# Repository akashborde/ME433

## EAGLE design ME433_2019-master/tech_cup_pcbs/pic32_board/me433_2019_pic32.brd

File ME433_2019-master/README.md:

# ME433_2019

Go to the wiki to see the syllabus and schedule.

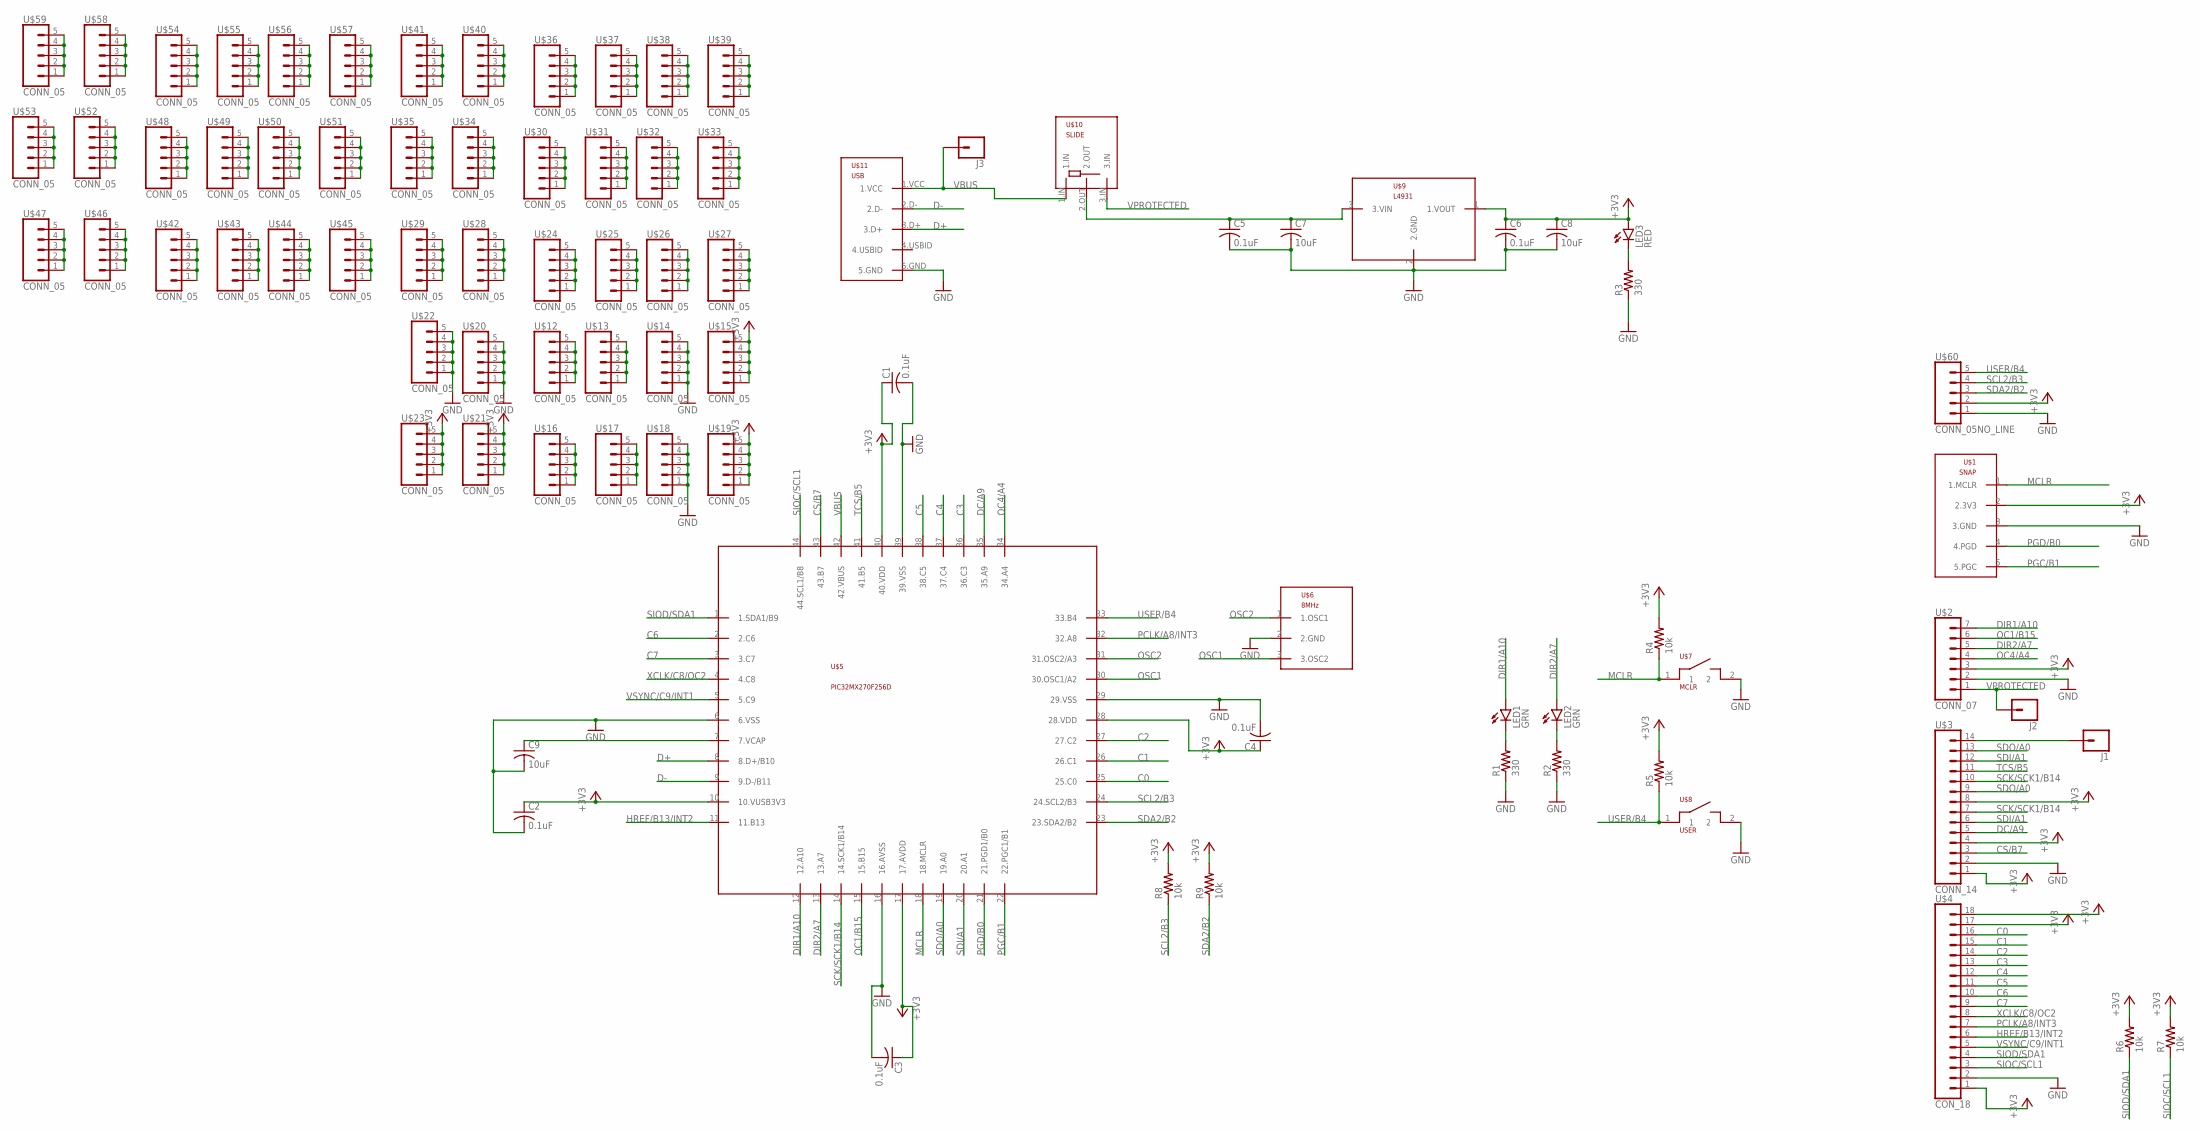
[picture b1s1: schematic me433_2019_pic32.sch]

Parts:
C1, C2, C3, C4, C5, C6: 0.1uF; C025-030X050
C7, C8, C9: 10uF; C025-030X050
J1, J2, J3: CONN_01; 1X01
LED1, LED2: GRN; LED3MM
LED3: RED; LED3MM
R1, R2, R3: 330; 0207/10
R4, R5, R6, R7, R8, R9: 10k; 0207/10
U$1: SNAP
U$2: CONN_07; 1X07
U$3: CONN_14; 1X14
U$4: CON_18; 1X18
U$5: PIC32MX270F256D; TQFP44
U$6: 8MHz; OSC
U$7: MCLR; PB
U$8: USER; PB
U$9: L4931
U$10: SLIDE
U$11: USB
U$12, U$13, U$14, U$15, U$16, U$17, U$18, U$19, U$20, U$21, U$22, U$23, U$24, U$25, U$26, U$27, U$28, U$29, U$30, U$31, U$32, U$33, U$34, U$35, U$36, U$37, U$38, U$39, U$40, U$41, U$42, U$43, U$44, U$45, U$46, U$47, U$48, U$49, U$50, U$51, U$52, U$53, U$54, U$55, U$56, U$57, U$58, U$59: CONN_05; 1X05
U$60: CONN_05NO_LINE; 1X05_NO_LINE

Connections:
+3V3: C1.1, C2.1, C3.1, C4.1, C6.1, C8.1, LED3.A, R4.2, R5.2, R6.2, R7.2, R8.2, R9.2, U$1.2 (2.3V3), U$2.3, U$3.1, U$3.4, U$3.8, U$4.1, U$4.17, U$4.18, U$5.10 (10.VUSB3V3), U$5.17 (17.AVDD), U$5.28 (28.VDD), U$5.40 (40.VDD), U$9.1 (1.VOUT), U$15.1, U$15.2, U$15.3, U$15.4, U$15.5, U$19.1, U$19.2, U$19.3, U$19.4, U$19.5, U$21.1, U$21.2, U$21.3, U$21.4, U$21.5, U$23.1, U$23.2, U$23.3, U$23.4, U$23.5, U$60.2
C0: U$4.16, U$5.25 (25.C0)
C1: U$4.15, U$5.26 (26.C1)
C2: U$4.14, U$5.27 (27.C2)
C3: U$4.13, U$5.36 (36.C3)
C4: U$4.12, U$5.37 (37.C4)
C5: U$4.11, U$5.38 (38.C5)
C6: U$4.10, U$5.2 (2.C6)
C7: U$4.9, U$5.3 (3.C7)
CS/B7: U$3.3, U$5.43 (43.B7)
D+: U$5.8 (8.D+/B10), U$11.3.D+
D-: U$5.9 (9.D-/B11), U$11.2.D-
DC/A9: U$3.5, U$5.35 (35.A9)
DIR1/A10: LED1.A, U$2.7, U$5.12 (12.A10)
DIR2/A7: LED2.A, U$2.5, U$5.13 (13.A7)
GND: C1.2, C2.2, C3.2, C4.2, C5.2, C6.2, C7.2, C8.2, C9.2, R1.1, R2.1, R3.1, U$1.3 (3.GND), U$2.2, U$3.2, U$4.2, U$5.6 (6.VSS), U$5.16 (16.AVSS), U$5.29 (29.VSS), U$5.39 (39.VSS), U$6.2 (2.GND), U$7.2, U$8.2, U$9.2 (2.GND), U$11.5.GND, U$14.1, U$14.2, U$14.3, U$14.4, U$14.5, U$18.1, U$18.2, U$18.3, U$18.4, U$18.5, U$20.1, U$20.2, U$20.3, U$20.4, U$20.5, U$22.1, U$22.2, U$22.3, U$22.4, U$22.5, U$60.1
HREF/B13/INT2: U$4.6, U$5.11 (11.B13)
MCLR: R4.1, U$1.1 (1.MCLR), U$5.18 (18.MCLR), U$7.1
unnamed: C9.1, U$5.7 (7.VCAP)
unnamed: LED1.K (C), R1.2
unnamed: LED2.K (C), R2.2
unnamed: J1.1, U$3.14
unnamed: C5.1, C7.1, U$9.3 (3.VIN), U$10.2.OUT
unnamed: U$12.1, U$12.2, U$12.3, U$12.4, U$12.5
unnamed: U$13.1, U$13.2, U$13.3, U$13.4, U$13.5
unnamed: LED3.K (C), R3.2
unnamed: U$16.1, U$16.2, U$16.3, U$16.4, U$16.5
unnamed: U$17.1, U$17.2, U$17.3, U$17.4, U$17.5
unnamed: U$24.1, U$24.2, U$24.3, U$24.4, U$24.5
unnamed: U$25.1, U$25.2, U$25.3, U$25.4, U$25.5
unnamed: U$26.1, U$26.2, U$26.3, U$26.4, U$26.5
unnamed: U$27.1, U$27.2, U$27.3, U$27.4, U$27.5
unnamed: U$28.1, U$28.2, U$28.3, U$28.4, U$28.5
unnamed: U$29.1, U$29.2, U$29.3, U$29.4, U$29.5
unnamed: U$30.1, U$30.2, U$30.3, U$30.4, U$30.5
unnamed: U$31.1, U$31.2, U$31.3, U$31.4, U$31.5
unnamed: U$32.1, U$32.2, U$32.3, U$32.4, U$32.5
unnamed: U$33.1, U$33.2, U$33.3, U$33.4, U$33.5
unnamed: U$34.1, U$34.2, U$34.3, U$34.4, U$34.5
unnamed: U$35.1, U$35.2, U$35.3, U$35.4, U$35.5
unnamed: U$36.1, U$36.2, U$36.3, U$36.4, U$36.5
unnamed: U$37.1, U$37.2, U$37.3, U$37.4, U$37.5
unnamed: U$38.1, U$38.2, U$38.3, U$38.4, U$38.5
unnamed: U$39.1, U$39.2, U$39.3, U$39.4, U$39.5
unnamed: U$40.1, U$40.2, U$40.3, U$40.4, U$40.5
unnamed: U$41.1, U$41.2, U$41.3, U$41.4, U$41.5
unnamed: U$42.1, U$42.2, U$42.3, U$42.4, U$42.5
unnamed: U$43.1, U$43.2, U$43.3, U$43.4, U$43.5
unnamed: U$44.1, U$44.2, U$44.3, U$44.4, U$44.5
unnamed: U$45.1, U$45.2, U$45.3, U$45.4, U$45.5
unnamed: U$46.1, U$46.2, U$46.3, U$46.4, U$46.5
unnamed: U$47.1, U$47.2, U$47.3, U$47.4, U$47.5
unnamed: U$48.1, U$48.2, U$48.3, U$48.4, U$48.5
unnamed: U$49.1, U$49.2, U$49.3, U$49.4, U$49.5
unnamed: U$50.1, U$50.2, U$50.3, U$50.4, U$50.5
unnamed: U$51.1, U$51.2, U$51.3, U$51.4, U$51.5
unnamed: U$52.1, U$52.2, U$52.3, U$52.4, U$52.5
unnamed: U$53.1, U$53.2, U$53.3, U$53.4, U$53.5
unnamed: U$54.1, U$54.2, U$54.3, U$54.4, U$54.5
unnamed: U$55.1, U$55.2, U$55.3, U$55.4, U$55.5
unnamed: U$56.1, U$56.2, U$56.3, U$56.4, U$56.5
unnamed: U$57.1, U$57.2, U$57.3, U$57.4, U$57.5
unnamed: U$58.1, U$58.2, U$58.3, U$58.4, U$58.5
unnamed: U$59.1, U$59.2, U$59.3, U$59.4, U$59.5
OC1/B15: U$2.6, U$5.15 (15.B15)
OC4/A4: U$2.4, U$5.34 (34.A4)
OSC1: U$5.30 (30.OSC1/A2), U$6.3 (3.OSC2)
OSC2: U$5.31 (31.OSC2/A3), U$6.1 (1.OSC1)
PCLK/A8/INT3: U$4.7, U$5.32 (32.A8)
PGC/B1: U$1.5 (5.PGC), U$5.22 (22.PGC1/B1)
PGD/B0: U$1.4 (4.PGD), U$5.21 (21.PGD1/B0)
SCK/SCK1/B14: U$3.7, U$3.10, U$5.14 (14.SCK1/B14)
SCL2/B3: R8.1, U$5.24 (24.SCL2/B3), U$60.4
SDA2/B2: R9.1, U$5.23 (23.SDA2/B2), U$60.3
SDI/A1: U$3.6, U$3.12, U$5.20 (20.A1)
SDO/A0: U$3.9, U$3.13, U$5.19 (19.A0)
SIOC/SCL1: R7.1, U$4.3, U$5.44 (44.SCL1/B8)
SIOD/SDA1: R6.1, U$4.4, U$5.1 (1.SDA1/B9)
TCS/B5: U$3.11, U$5.41 (41.B5)
USER/B4: R5.1, U$5.33 (33.B4), U$8.1, U$60.5
VBUS: J3.1, U$5.42 (42.VBUS), U$10.1.IN, U$11.1.VCC
VPROTECTED: J2.1, U$2.1, U$10.3.IN
VSYNC/C9/INT1: U$4.5, U$5.5 (5.C9)
XCLK/C8/OC2: U$4.8, U$5.4 (4.C8)

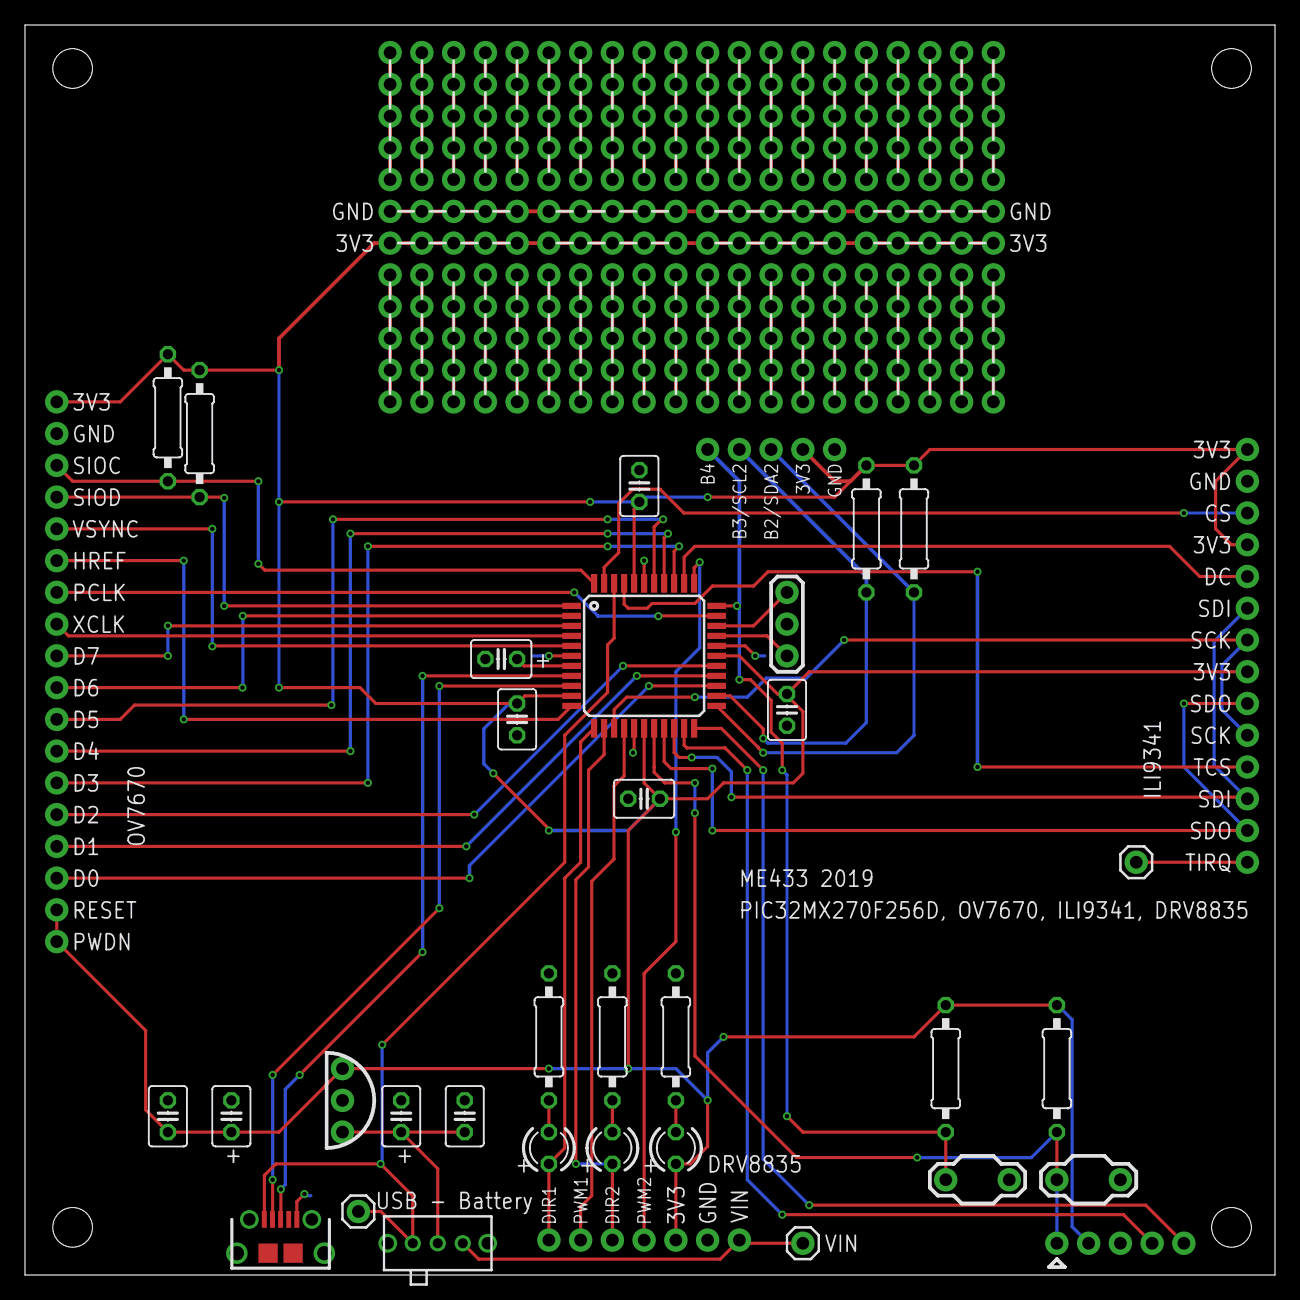
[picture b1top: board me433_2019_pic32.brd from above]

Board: 2 copper layers, 100.0 x 100.0 mm, 84 parts (0 on the bottom side), 84 nets.

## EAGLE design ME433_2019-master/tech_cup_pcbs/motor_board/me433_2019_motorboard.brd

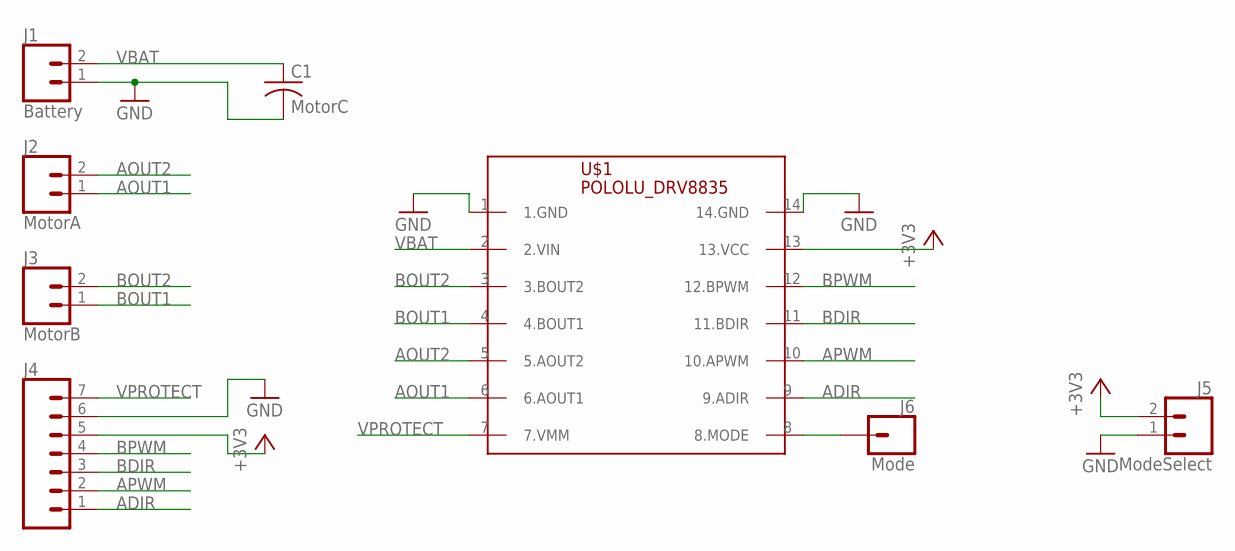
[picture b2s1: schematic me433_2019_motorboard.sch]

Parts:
C1: MotorC; C050-030X075
J1: Battery; 1X02
J2: MotorA; 1X02
J3: MotorB; 1X02
J4: CONN_07; 1X07
J5: ModeSelect; 1X02
J6: Mode; 1X01
U$1: POLOLU_DRV8835; DIL14

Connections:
+3V3: J4.5, J5.2, U$1.13 (13.VCC)
ADIR: J4.1, U$1.9 (9.ADIR)
AOUT1: J2.1, U$1.6 (6.AOUT1)
AOUT2: J2.2, U$1.5 (5.AOUT2)
APWM: J4.2, U$1.10 (10.APWM)
BDIR: J4.3, U$1.11 (11.BDIR)
BOUT1: J3.1, U$1.4 (4.BOUT1)
BOUT2: J3.2, U$1.3 (3.BOUT2)
BPWM: J4.4, U$1.12 (12.BPWM)
GND: C1.2, J1.1, J4.6, J5.1, U$1.1 (1.GND), U$1.14 (14.GND)
unnamed: J6.1, U$1.8 (8.MODE)
VBAT: C1.1, J1.2, U$1.2 (2.VIN)
VPROTECT: J4.7, U$1.7 (7.VMM)

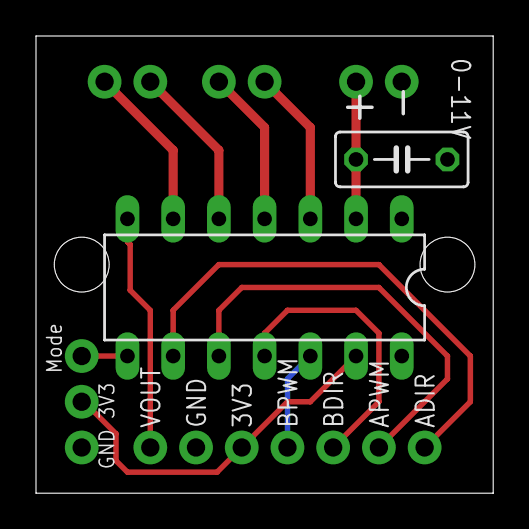
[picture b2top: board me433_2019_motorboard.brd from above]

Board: 2 copper layers, 25.4 x 25.4 mm, 8 parts (0 on the bottom side), 13 nets.

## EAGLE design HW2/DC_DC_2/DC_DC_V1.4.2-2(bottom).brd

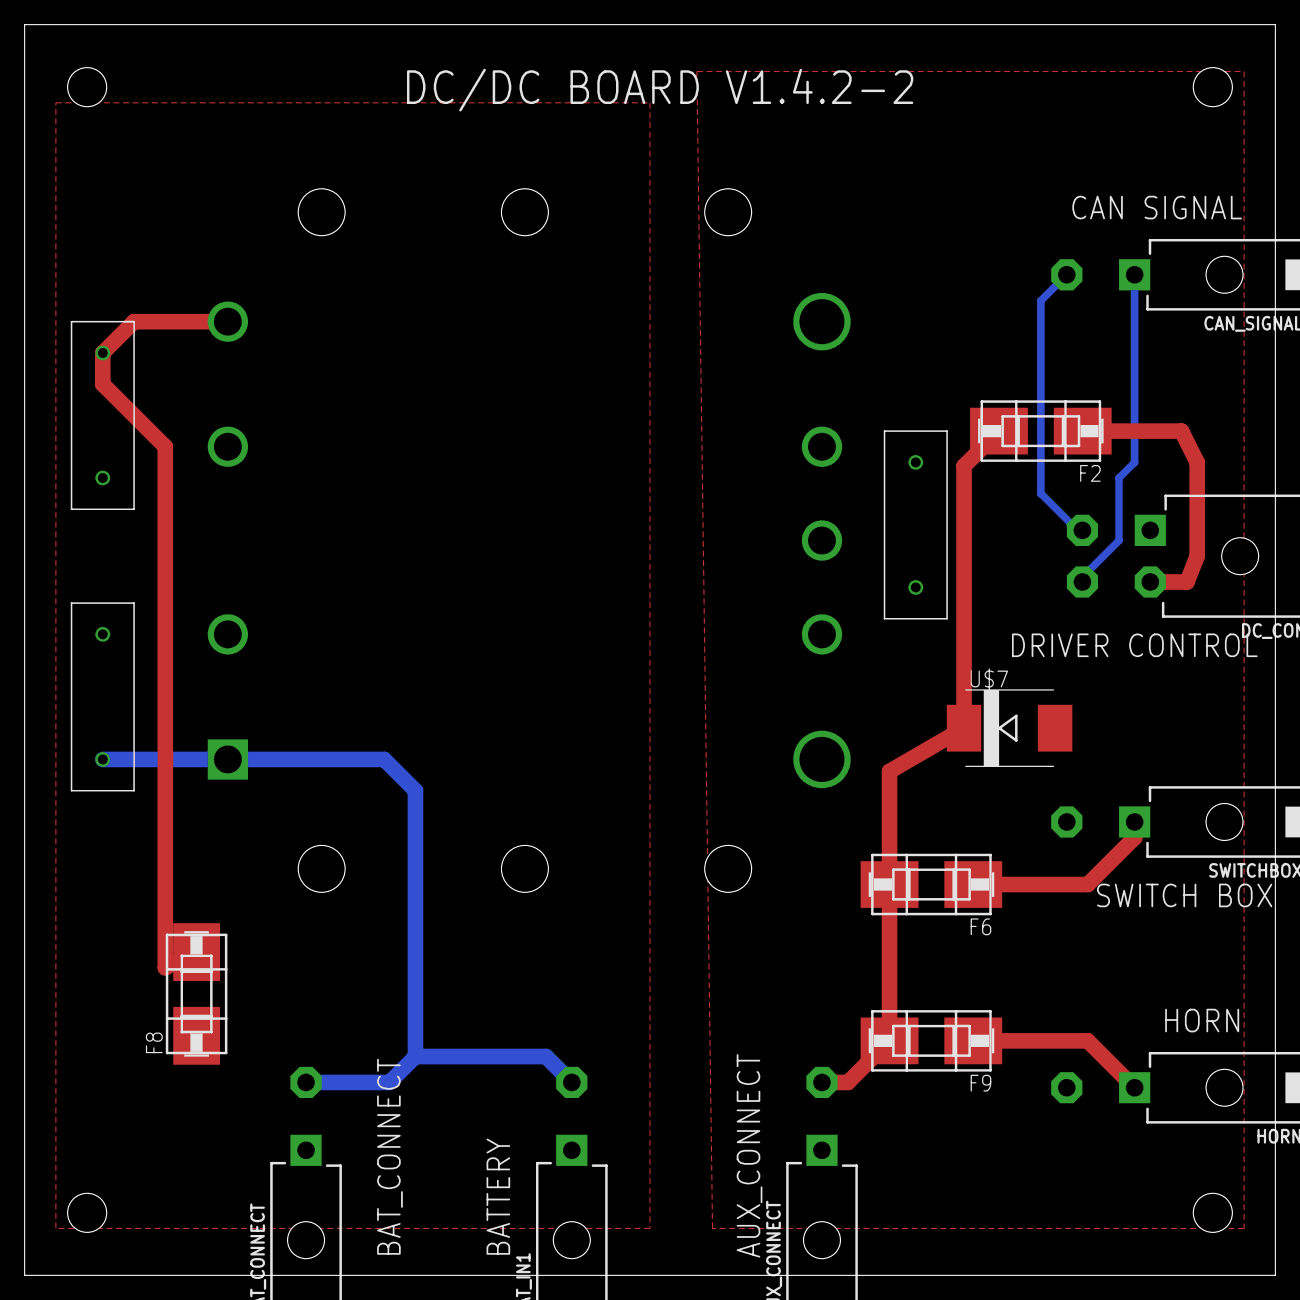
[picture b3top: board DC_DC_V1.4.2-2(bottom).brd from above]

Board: 2 copper layers, 101.6 x 101.6 mm, 16 parts (0 on the bottom side), 11 nets.

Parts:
AUX_CONNECT: 39-30-02?_S; 39-30-?02?
BAT_CONNECT: 39-30-02?_S; 39-30-?02?
BAT_IN1: 39-30-02?_S; 39-30-?02?
CAN_SIGNAL: 39-30-02?_S; 39-30-?02?
DC_CONN: 39-30-04?; 39-30-?04?
F2, F9: 1.5A; OMNIBLOK
F6: 4A; OMNIBLOK
F8: 2A; OMNIBLOK
HORN: 39-30-02?_S; 39-30-?02?
SWITCHBOX: 39-30-02?_S; 39-30-?02?
U$7: SL44HE3; SMC
U$8, U$9, U$10: 4700PF; Y2_CAP
U$11: VI-JT1-EW; VI-J00

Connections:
12V: U$7.A, U$10.P$2, U$11.P$8, U$11.P$9
CAN_H: CAN_SIGNAL.1, DC_CONN.4
CAN_L: CAN_SIGNAL.2, DC_CONN.3
GND: AUX_CONNECT.1, DC_CONN.1, HORN.2, SWITCHBOX.2, U$8.P$2, U$9.P$1, U$10.P$1, U$11.P$5, U$11.P$6
IN+: BAT_CONNECT.1, BAT_IN1.1, F8.P$1
IN-: BAT_CONNECT.2, BAT_IN1.2, U$8.P$1, U$11.P$1
unnamed: AUX_CONNECT.2, F2.P$2, F6.P$2, F9.P$2, U$7.C
unnamed: DC_CONN.2, F2.P$1
unnamed: F6.P$1, SWITCHBOX.1
unnamed: F9.P$1, HORN.1
unnamed: F8.P$2, U$9.P$2, U$11.P$4

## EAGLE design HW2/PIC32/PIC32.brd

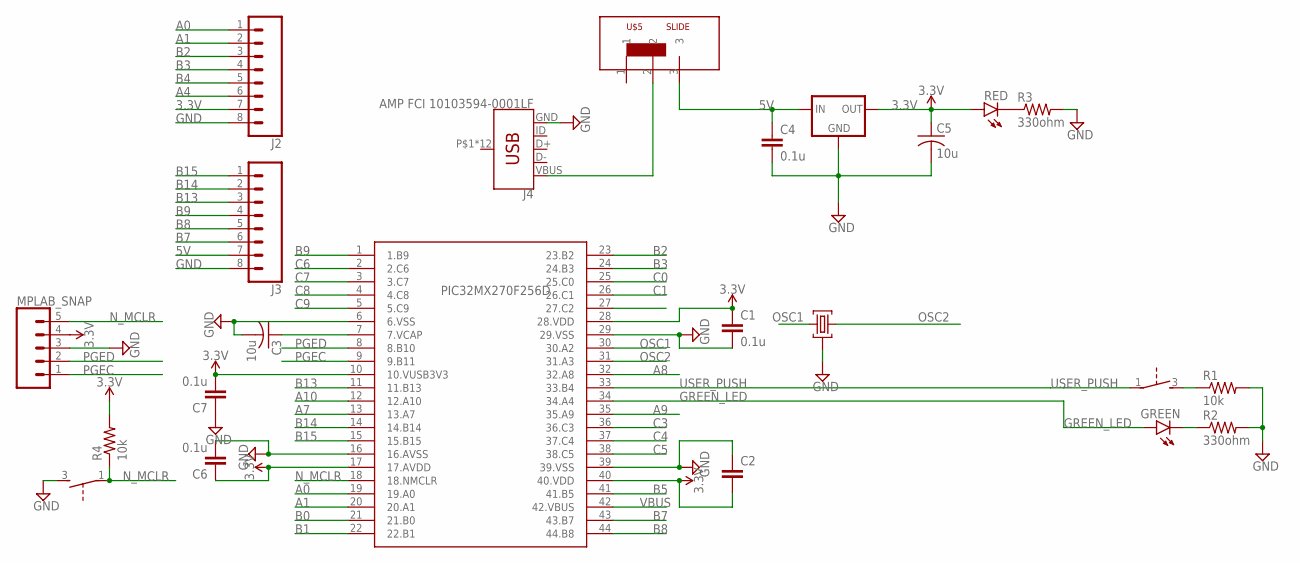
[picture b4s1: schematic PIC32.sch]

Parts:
C1, C4, C6, C7: 0.1u; C2.5-3
C2: C2,5-3; C2.5-3
C3, C5: 10u; C050-045X075
GREEN: LED3MM
J2, J3: CONN_08"; 1X08
J4: AMP FCI 10103594-0001LF; USB-MICROB-PTH
MPLAB_SNAP: CONN_05; 1X05
R1, R4: 10k; 0207/7
R2, R3: 330ohm; 0207/7
RED: LED3MM
U$1: PIC32MX270F256D
U$2: 8MHZ_XTAL
U$3: EVQ-11
U$4: L4931; TO92
U$5: SLIDE
USER_PUSH: EVQ-11

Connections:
3.3V: C1.1, C2.2, C5.1, C6.1, C7.2, J2.7, MPLAB_SNAP.4, R4.2, RED.A, U$1.10 (10.VUSB3V3), U$1.17 (17.AVDD), U$1.28 (28.VDD), U$1.40 (40.VDD), U$4.VOUT (OUT)
5V: C4.1, J3.7, U$4.VIN (IN), U$5.3
A0: J2.1, U$1.19 (19.A0)
A1: J2.2, U$1.20 (20.A1)
A4: J2.6
A7: U$1.13 (13.A7)
A8: U$1.32 (32.A8)
A9: U$1.35 (35.A9)
A10: U$1.12 (12.A10)
B0: U$1.21 (21.B0)
B1: U$1.22 (22.B1)
B2: J2.3, U$1.23 (23.B2)
B3: J2.4, U$1.24 (24.B3)
B4: J2.5
B5: U$1.41 (41.B5)
B7: J3.6, U$1.43 (43.B7)
B8: J3.5, U$1.44 (44.B8)
B9: J3.4, U$1.1 (1.B9)
B13: J3.3, U$1.11 (11.B13)
B14: J3.2, U$1.14 (14.B14)
B15: J3.1, U$1.15 (15.B15)
C0: U$1.25 (25.C0)
C1: U$1.26 (26.C1)
C3: U$1.36 (36.C3)
C4: U$1.37 (37.C4)
C5: U$1.38 (38.C5)
C6: U$1.2 (2.C6)
C7: U$1.3 (3.C7)
C8: U$1.4 (4.C8)
C9: U$1.5 (5.C9)
GND: C1.2, C2.1, C3.2, C4.2, C5.2, C6.2, C7.1, J2.8, J3.8, J4.GND, MPLAB_SNAP.3, R1.2, R2.2, R3.2, U$1.6 (6.VSS), U$1.16 (16.AVSS), U$1.29 (29.VSS), U$1.39 (39.VSS), U$2.2, U$3.3 (S), U$4.GND
GREEN_LED: GREEN.A, U$1.34 (34.A4)
unnamed: R1.1, USER_PUSH.3 (S)
unnamed: GREEN.K (C), R2.1
unnamed: R3.1, RED.K (C)
unnamed: C3.1, U$1.7 (7.VCAP)
unnamed: J4.VBUS, U$5.2
N_MCLR: MPLAB_SNAP.5, R4.1, U$1.18 (18.NMCLR), U$3.1
OSC1: U$1.30 (30.A2), U$2.1
OSC2: U$1.31 (31.A3), U$2.3
PGEC: MPLAB_SNAP.1, U$1.9 (9.B11)
PGED: MPLAB_SNAP.2, U$1.8 (8.B10)
USER_PUSH: U$1.33 (33.B4), USER_PUSH.1
VBUS: U$1.42 (42.VBUS)

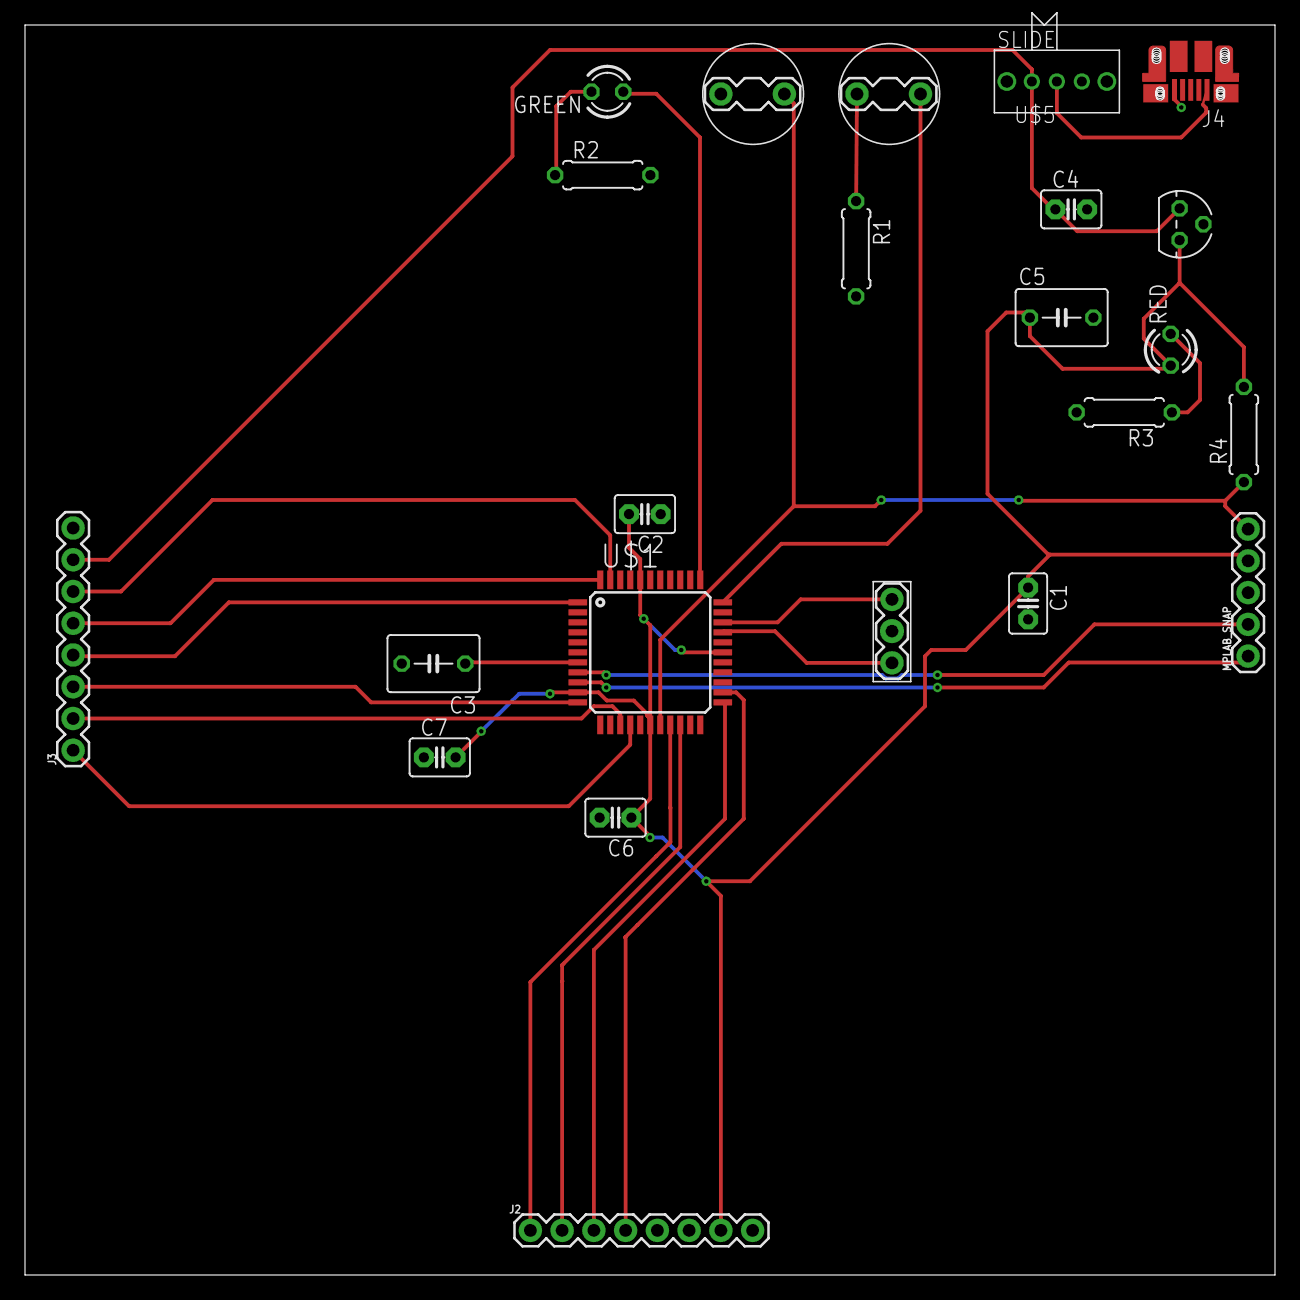
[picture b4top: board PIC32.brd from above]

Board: 2 copper layers, 100.0 x 100.0 mm, 23 parts (0 on the bottom side), 25 nets.

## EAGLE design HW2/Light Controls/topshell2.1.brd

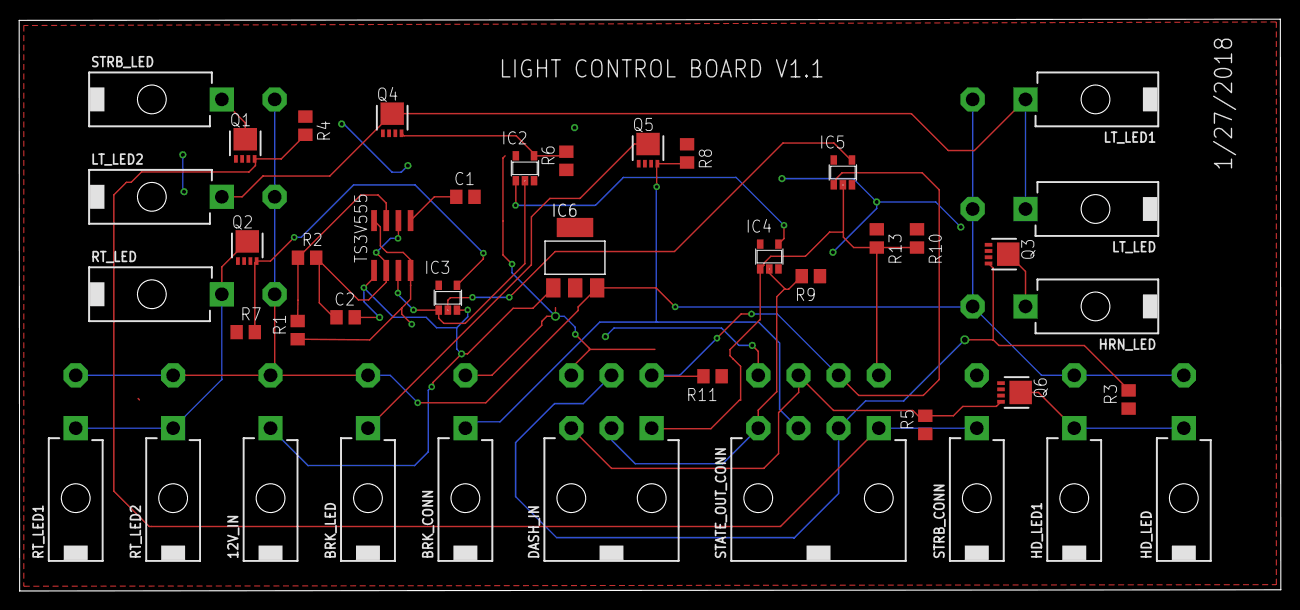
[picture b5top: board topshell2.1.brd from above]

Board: 2 copper layers, 131.6 x 59.6 mm, 42 parts (0 on the bottom side), 25 nets.

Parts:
12V_IN: 39-30-02?; 39-30-?02?
BRK_CONN: 39-30-02?; 39-30-?02?
BRK_LED: 39-30-02?; 39-30-?02?
C1: 10nF; C0805
C2: 2.2uF; C0805
DASH_IN: 39-30-06?; 39-30-?06?
HD_LED, HD_LED1: 39-30-02?; 39-30-?02?
HRN_LED: 39-30-02?; 39-30-?02?
IC2, IC3: 74AHC1G08DBV; SOT23-5
IC4, IC5: 74AHC1G32DBV; SOT23-5
IC6: REG1117; SOT223
LT_LED, LT_LED1, LT_LED2: 39-30-02?; 39-30-?02?
Q1, Q2, Q3, Q4, Q5, Q6: PSMN013-30MLC; LFPAK33
R1: 100K; R0805
R2: 220K; R0805
R3, R4, R5, R6, R7, R8, R9, R10, R11, R13: 1K; R0805
RT_LED, RT_LED1, RT_LED2: 39-30-02?; 39-30-?02?
STATE_OUT_CONN: 39-30-08?; 39-30-?08?
STRB_CONN: 39-30-02?; 39-30-?02?
STRB_LED: 39-30-02?; 39-30-?02?
TS3V555: LM555D; SO08

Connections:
12V: 12V_IN.2, BRK_LED.2, HD_LED.2, HD_LED1.2, HRN_LED.2, IC6.3, LT_LED.2, LT_LED1.2, LT_LED2.2, RT_LED.2, RT_LED1.2, RT_LED2.2, STRB_LED.2
GND: 12V_IN.1, C1.2, C2.2, IC2.3, IC3.3, IC4.3, IC5.3, IC6.1, Q1.1, Q1.2, Q1.3, Q2.1, Q2.2, Q2.3, Q3.1, Q3.2, Q3.3, Q4.1, Q4.2, Q4.3, Q5.1, Q5.2, Q5.3, Q6.1, Q6.2, Q6.3, R3.1, R4.1, R5.1, R6.1, R7.1, R8.1, R9.1, R10.1, R11.1, R13.1, STATE_OUT_CONN.8, STRB_CONN.2, TS3V555.1
unnamed: R1.2, R2.1, TS3V555.7
unnamed: Q1.MB, STRB_LED.1
unnamed: C2.1, R2.2, TS3V555.2, TS3V555.6
unnamed: IC2.2, IC3.1, TS3V555.3
unnamed: HRN_LED.1, Q3.MB
unnamed: Q1.4, R4.2, STATE_OUT_CONN.1, STRB_CONN.1
unnamed: DASH_IN.2, IC4.2, R9.2, STATE_OUT_CONN.4
unnamed: DASH_IN.1, IC4.1, IC5.2, R10.2, R13.2, STATE_OUT_CONN.5
unnamed: IC2.1, IC4.4
unnamed: IC3.2, IC5.4
unnamed: DASH_IN.4, IC5.1, R11.2, STATE_OUT_CONN.6
unnamed: IC2.4, Q4.4, R6.2
unnamed: IC3.4, Q2.4, R7.2
unnamed: LT_LED.1, LT_LED1.1, LT_LED2.1, Q4.MB
unnamed: Q2.MB, RT_LED.1, RT_LED1.1, RT_LED2.1
unnamed: BRK_LED.1, Q5.MB
unnamed: HD_LED.1, HD_LED1.1, Q6.MB
unnamed: DASH_IN.3, Q6.4, R5.2, STATE_OUT_CONN.7
unnamed: DASH_IN.5, Q3.4, R3.2, STATE_OUT_CONN.2
unnamed: BRK_CONN.1, Q5.4, R8.2, STATE_OUT_CONN.3
TS3V555: C1.1, TS3V555.5
VCC: BRK_CONN.2, DASH_IN.6, R1.1, TS3V555.4, TS3V555.8
VCC_3.3V: IC2.5, IC3.5, IC4.5, IC5.5, IC6.2

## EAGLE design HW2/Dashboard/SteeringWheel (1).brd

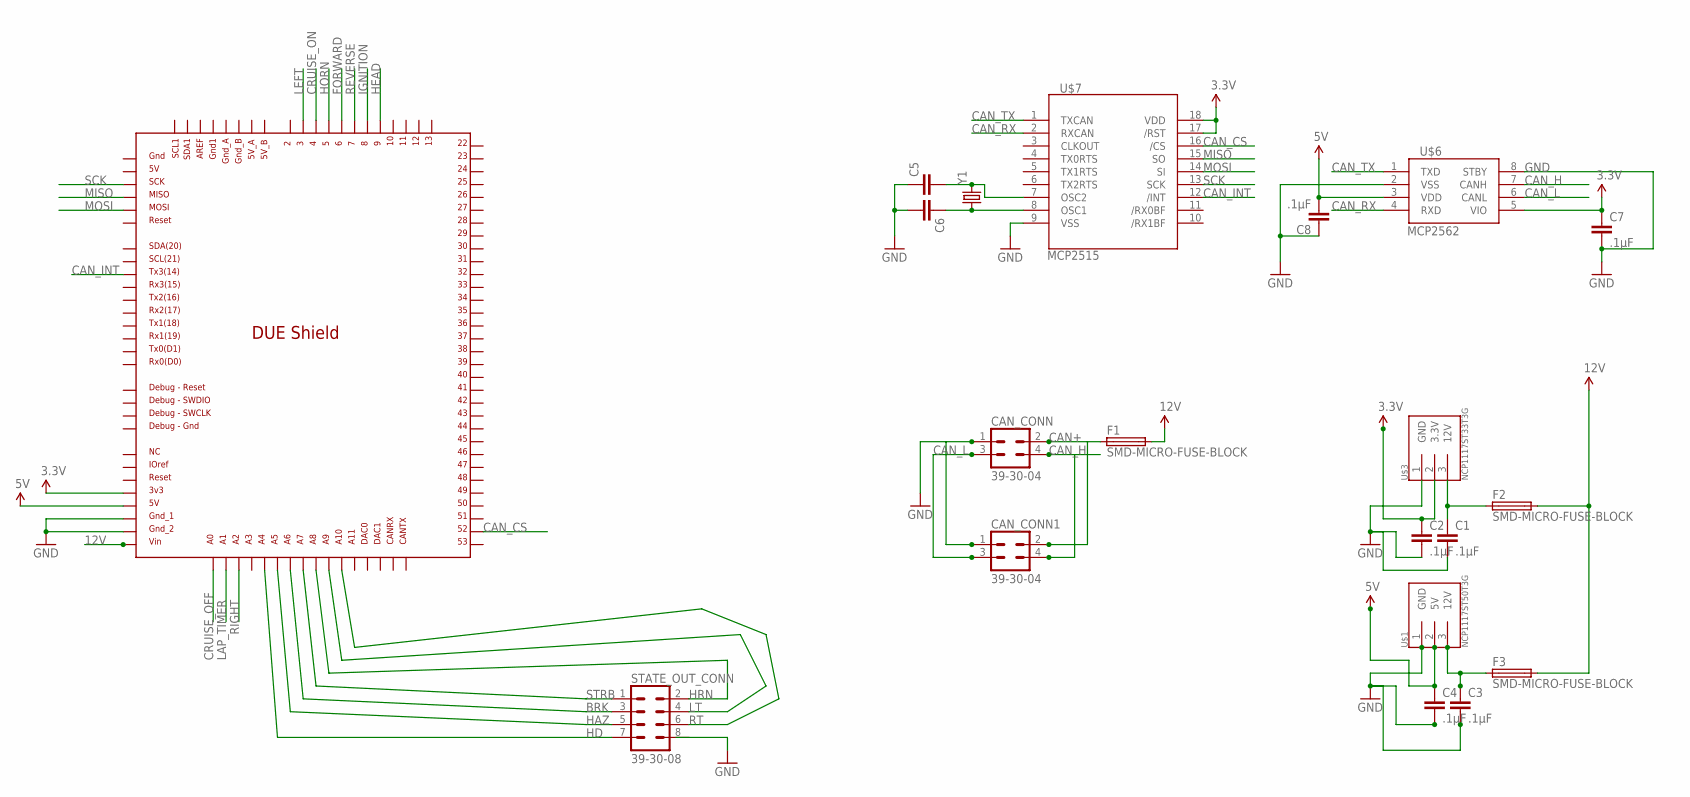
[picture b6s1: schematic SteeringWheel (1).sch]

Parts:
C1, C2, C3, C4, C7, C8: .1µF; 0805
C5, C6: CAP0805; 0805
CAN_CONN, CAN_CONN1: 39-30-04; 39-30-?04?
F1, F2, F3: SMD-MICRO-FUSE-BLOCK; OMNIBLOK
STATE_OUT_CONN: 39-30-08; 39-30-?08?
U$1: NCP1117ST50T3G; SOT223
U$2: DUE(NORMAL)
U$3: NCP1117ST33T3G; SOT223
U$6: MCP2562; SOIC8
U$7: MCP2515; SO-18W
Y1: CRYSTALHC49US; HC49US

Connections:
3.3V: C2.1, C7.1, U$2.3V3, U$3.2 (3.3V), U$6.5 (VIO), U$7.17 (/RST), U$7.18 (VDD)
5V: C4.1, C8.2, U$1.2 (5V), U$2.5V, U$6.3 (VDD)
12V: F1.P$2 (2), F2.P$2 (2), F3.P$2 (2), U$2.VIN
BRK: STATE_OUT_CONN.3, U$2.A6
CAN+: CAN_CONN.2, CAN_CONN1.2, F1.P$1 (1)
CAN_CS: U$2.52, U$7.16 (/CS)
CAN_H: CAN_CONN.4, CAN_CONN1.4, U$6.7 (CANH)
CAN_INT: U$2.TX3, U$7.12 (/INT)
CAN_L: CAN_CONN.3, CAN_CONN1.3, U$6.6 (CANL)
CAN_RX: U$6.4 (RXD), U$7.2 (RXCAN)
CAN_TX: U$6.1 (TXD), U$7.1 (TXCAN)
CRUISE_OFF: U$2.A0
CRUISE_ON: U$2.4
FORWARD: U$2.6
GND: C1.2, C2.2, C3.2, C4.2, C5.1, C6.2, C7.2, C8.1, CAN_CONN.1, CAN_CONN1.1, U$1.1 (GND), U$2.GND_1, U$2.GND_2, U$3.1 (GND), U$6.2 (VSS), U$6.8 (STBY), U$7.9 (VSS)
HAZ: STATE_OUT_CONN.5, U$2.A5
HD: STATE_OUT_CONN.7, U$2.A4
HEAD: U$2.9
HORN: U$2.5
HRN: STATE_OUT_CONN.2, U$2.A8
IGNITION: U$2.8
LAP_TIMER: U$2.A1
LEFT: U$2.3
LT: STATE_OUT_CONN.4, U$2.A9
MISO: U$2.MISO_ICSP, U$7.15 (SO)
MOSI: U$2.MOSI_ICSP, U$7.14 (SI)
unnamed: C3.1, F3.P$1 (1), U$1.3 (12V)
unnamed: C1.1, F2.P$1 (1), U$3.3 (12V)
unnamed: C5.2, U$7.7 (OSC2), Y1.2
unnamed: C6.1, U$7.8 (OSC1), Y1.1
REVERSE: U$2.7
RIGHT: U$2.A2
RT: STATE_OUT_CONN.6, U$2.A10
SCK: U$2.SCK_ICSP, U$7.13 (SCK)
STRB: STATE_OUT_CONN.1, U$2.A7

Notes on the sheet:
CAN_CS
CAN_INT
STRB
HRN
HAZ
BRK

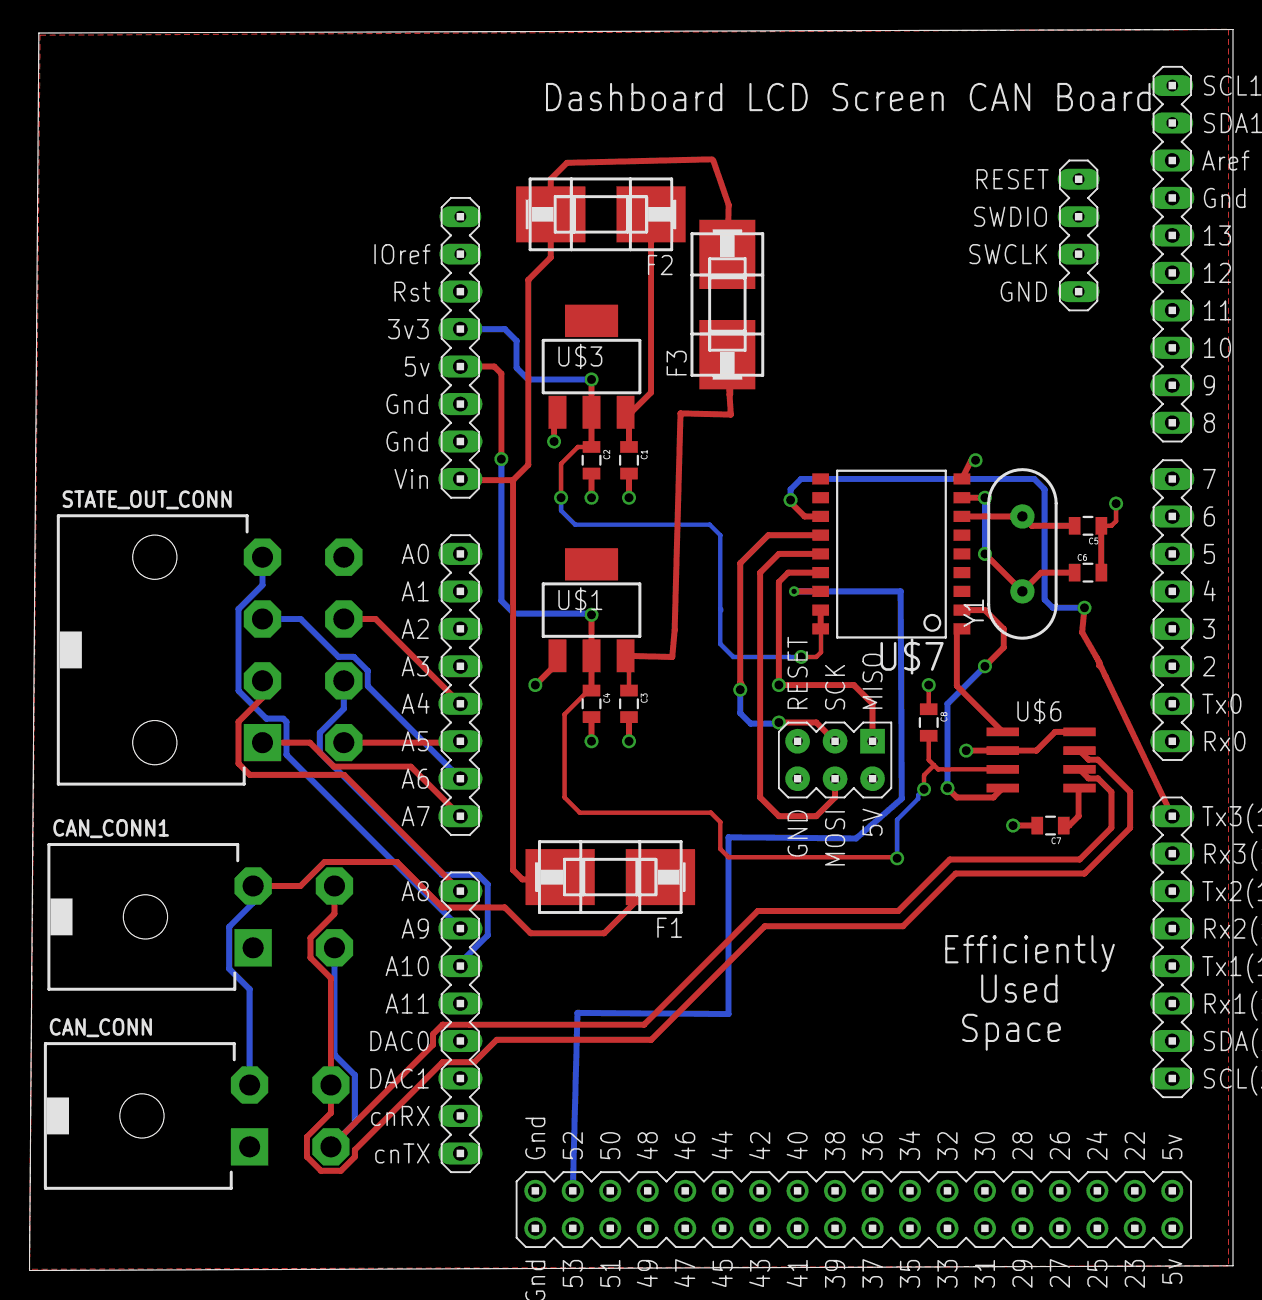
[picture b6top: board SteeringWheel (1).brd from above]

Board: 2 copper layers, 81.6 x 84.1 mm, 20 parts (0 on the bottom side), 25 nets.

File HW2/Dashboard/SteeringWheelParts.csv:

"Part";"Value";"Device";"Package";"Description";"";
"C1";".1µF";"CAP0805";"0805";"Capacitor";"";
"C2";".1µF";"CAP0805";"0805";"Capacitor";"";
"C3";".1µF";"CAP0805";"0805";"Capacitor";"";
"C4";".1µF";"CAP0805";"0805";"Capacitor";"";
"C5";"";"CAP0805";"0805";"Capacitor";"";
"C6";"";"CAP0805";"0805";"Capacitor";"";
"C7";".1µF";"CAP0805";"0805";"Capacitor";"";
"C8";".1µF";"CAP0805";"0805";"Capacitor";"";
"CAN_CONN";"39-30-04?";"39-30-04?";"39-30-?04?";"HEADER";"";
"CAN_CONN1";"39-30-04?";"39-30-04?";"39-30-?04?";"HEADER";"";
"F1";"SMD-MICRO-FUSE-BLOCK";"SMD-MICRO-FUSE-BLOCK";"OMNIBLOK";"";"";
"F2";"SMD-MICRO-FUSE-BLOCK";"SMD-MICRO-FUSE-BLOCK";"OMNIBLOK";"";"";
"F3";"SMD-MICRO-FUSE-BLOCK";"SMD-MICRO-FUSE-BLOCK";"OMNIBLOK";"";"";
"STATE_OUT_CONN";"39-30-08?";"39-30-08?";"39-30-?08?";"HEADER";"";
"U$1";"NCP1117ST50T3G";"NCP1117ST50T3G";"SOT223";"";"";
"U$2";"DUE(NORMAL)";"DUE(NORMAL)";"DUE(NORMAL)";"";"";
"U$3";"NCP1117ST33T3G";"NCP1117ST33T3G";"SOT223";"";"";
"U$6";"MCP2562";"MCP2562";"SOIC8";"";"";
"U$7";"MCP2515";"MCP2515";"SO-18W";"";"";
"Y1";"";"CRYSTALHC49US";"HC49US";"Various standard crystals. Proven footprints.";"";

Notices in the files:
parts and their libraries:
con-molex-mini-fit: Copyright (C) 2011, Bob Starr
SparkFun-Capacitors: Licensing: Creative Commons ShareAlike 4.0 International - https://creativecommons.org/licenses/by-sa/4.0
transistor-power: PSMN013-30MLC © NXP B.V. 2012. All rights reserved.
